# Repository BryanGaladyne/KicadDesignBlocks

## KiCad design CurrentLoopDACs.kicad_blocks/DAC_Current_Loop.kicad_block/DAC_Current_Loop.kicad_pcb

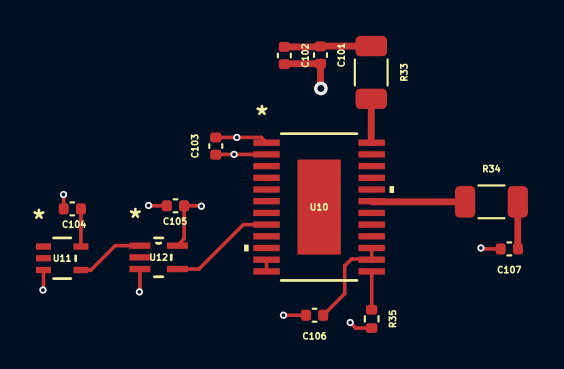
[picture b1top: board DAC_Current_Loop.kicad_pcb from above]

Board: 2 copper layers, 13 parts (0 on the bottom side), 11 nets.

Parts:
C101: 100p; C_0402_1005Metric
C102, C103, C104, C105, C106, C107: 0.1u; C_0402_1005Metric
R33: 10; R_1206_3216Metric
R34: 15; R_1206_3216Metric
R35: 15K; R_0402_1005Metric
U10: DAC7750IPWPR; PWP24_TEX
U11: NC7SZ04P5X; SC-88A-5_1P35X2P2_ONS
U12: SN74LVC1G08DCKR; DCK5

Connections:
+3.3VP: C103.1, C104.1, C105.1, U10.2 (DVDD), U11.5 (VCC), U12.5 (VCC)
+12V: C101.1, C102.1, R33.1
/DAC/AVDD: R33.2, U10.24 (AVDD)
/DAC/CURRENT_OUT: C107.1, R34.2
/DAC/IOUT: R34.1, U10.19 (IOUT)
/DAC/ISET_R: R35.1, U10.13 (ISET-R)
/DAC/LATCH: U10.7 (LATCH), U11.2 (A)
/DAC/LATCH_N: U11.4 (A_N=Y), U12.1 (A)
/DAC/REFOUT: C106.1, U10.14 (REFOUT), U10.15 (REFIN)
/DAC/SCLK_AND_LATCH_N: U10.8 (SCLK), U12.4 (Y)
GND: C101.2, C102.2, C103.2, C104.2, C105.2, C106.2, C107.2, R35.2, U10.1 (GND), U10.4 (GND), U10.5 (GND), U10.11 (GND), U10.12 (GND), U11.3 (GND), U12.3 (GND)

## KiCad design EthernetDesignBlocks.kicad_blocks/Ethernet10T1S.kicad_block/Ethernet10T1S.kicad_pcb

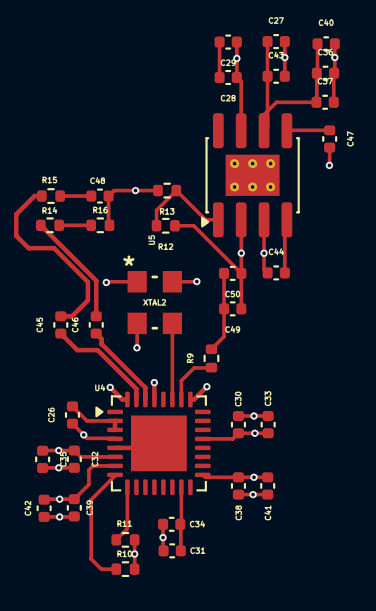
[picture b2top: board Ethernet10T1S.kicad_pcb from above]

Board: 2 copper layers, 36 parts (0 on the bottom side), 15 nets.

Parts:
C26, C27, C28, C29: 10u; C_0402_1005Metric
C30, C31, C32, C38, C39: 10n; C_0402_1005Metric
C33, C34, C35, C41, C42, C45, C46, C48: .1U; C_0402_1005Metric
C36, C37, C40, C43, C44, C47, C50: 1u; C_0402_1005Metric
C49: 100n; C_0402_1005Metric
R9: 12.4K; R_0402_1005Metric
R10, R11: 10K; R_0402_1005Metric
R12: 2.94K; R_0402_1005Metric
R13: 1.13K; R_0402_1005Metric
R14, R15: 49.9K; R_0402_1005Metric
R16: 100K; R_0402_1005Metric
U4: LAN8650B1-E/LMX; QFN-32-1EP_5x5mm_P0.5mm_EP3.1x3.1mm
U5: LP38852MRX-ADJ/NOPB; SOIC-8-1EP_3.9x4.9mm_P1.27mm_EP2.29x3mm_ThermalVias
XTAL2: ECS-2520S33-250-FN-TR; ECS-2520S_ECS

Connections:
+3V3: C26.1, C27.1, C28.1, C29.1, C36.1, C37.1, C38.1, C39.1, C40.1, C41.1, C42.1, C43.1, R10.2, R11.2, U4.4 (TEST), U4.7 (VDDP), U4.17 (VDDP), U4.25 (VDDAU), U4.29 (VDDA), U5.6 (EN), U5.7 (IN), XTAL2.1 (TRI-STATE), XTAL2.4 (VDD)
+5V: C44.1, U5.3 (BIAS)
/Ethernet2/1V8: C30.1, C31.1, C32.1, C33.1, C34.1, C35.1, C49.1, C50.1, R12.1, U4.6 (VDDC), U4.15 (VDDC), U4.21 (VDDC), U5.2 (OUT)
/Ethernet2/BIAS: R9.1, U4.26 (RBIAS)
/Ethernet2/ETH_10T1S_TRXN: C45.2, R15.1
/Ethernet2/ETH_10T1S_TRXP: C46.2, R14.1
/Ethernet2/IRQ_N: R11.1, U4.9 (IRQ_N)
/Ethernet2/RESET_N: R10.1, U4.8 (RESET_N)
/Ethernet2/TRXN: C45.1, U4.31 (TRXN)
/Ethernet2/TRXP: C46.1, U4.30 (TRXP)
/Ethernet2/U3_ADJ: R12.2, R13.1, U5.1 (ADJ)
/Ethernet2/U3_SS: C47.1, U5.5 (SS)
/Ethernet2/XTI_U2: U4.27 (XTI), XTAL2.3 (OUTPUT)
GND: C26.2, C27.2, C28.2, C29.2, C30.2, C31.2, C32.2, C33.2, C34.2, C35.2, C36.2, C37.2, C38.2, C39.2, C40.2, C41.2, C42.2, C43.2, C44.2, C47.2, C48.1, C49.2, C50.2, R9.2, R13.2, R16.2, U4.2 (VSS), U4.3 (VSS), U4.5 (VSS), U4.33 (VSS), U5.4 (GND), XTAL2.2 (GND)
unnamed: C48.2, R14.2, R15.2, R16.1

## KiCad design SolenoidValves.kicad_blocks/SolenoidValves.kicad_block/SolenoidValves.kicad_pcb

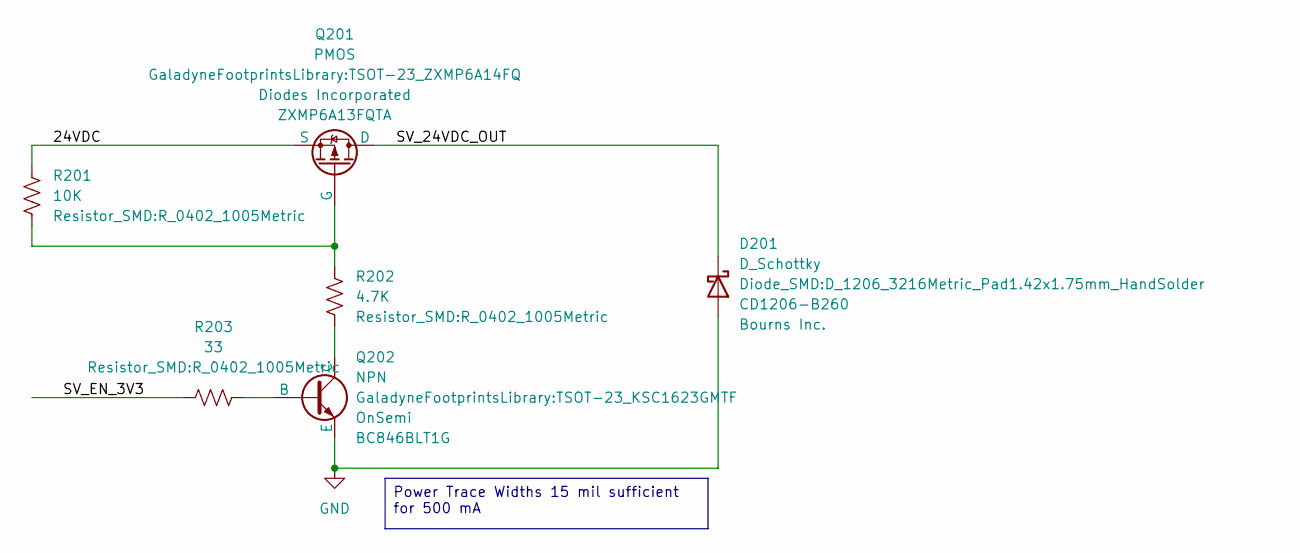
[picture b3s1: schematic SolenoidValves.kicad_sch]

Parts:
D201: D_Schottky; D_1206_3216Metric_Pad1.42x1.75mm_HandSolder; MPN CD1206-B260
Q201: PMOS; TSOT-23_ZXMP6A14FQ; MPN ZXMP6A13FQTA
Q202: NPN; TSOT-23_KSC1623GMTF; MPN BC846BLT1G
R201: 10K; R_0402_1005Metric
R202: 4.7K; R_0402_1005Metric
R203: 33; R_0402_1005Metric

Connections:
/SolenoidValves/24VDC: Q201.3 (S), R201.1
/SolenoidValves/SV_24VDC_OUT: D201.1 (K), Q201.1 (D)
/SolenoidValves/SV_EN_3V3: R203.1
GND: D201.2 (A), Q202.3 (E)
unnamed: Q201.2 (G), R201.2, R202.1
unnamed: Q202.2 (B), R203.2
unnamed: Q202.1 (C), R202.2

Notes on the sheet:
Power Trace Widths 15 mil sufficient for 500 mA

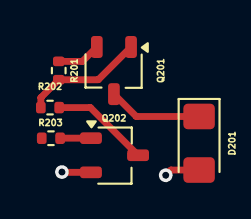
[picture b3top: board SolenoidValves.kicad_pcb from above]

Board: 2 copper layers, 6 parts (0 on the bottom side), 6 nets.

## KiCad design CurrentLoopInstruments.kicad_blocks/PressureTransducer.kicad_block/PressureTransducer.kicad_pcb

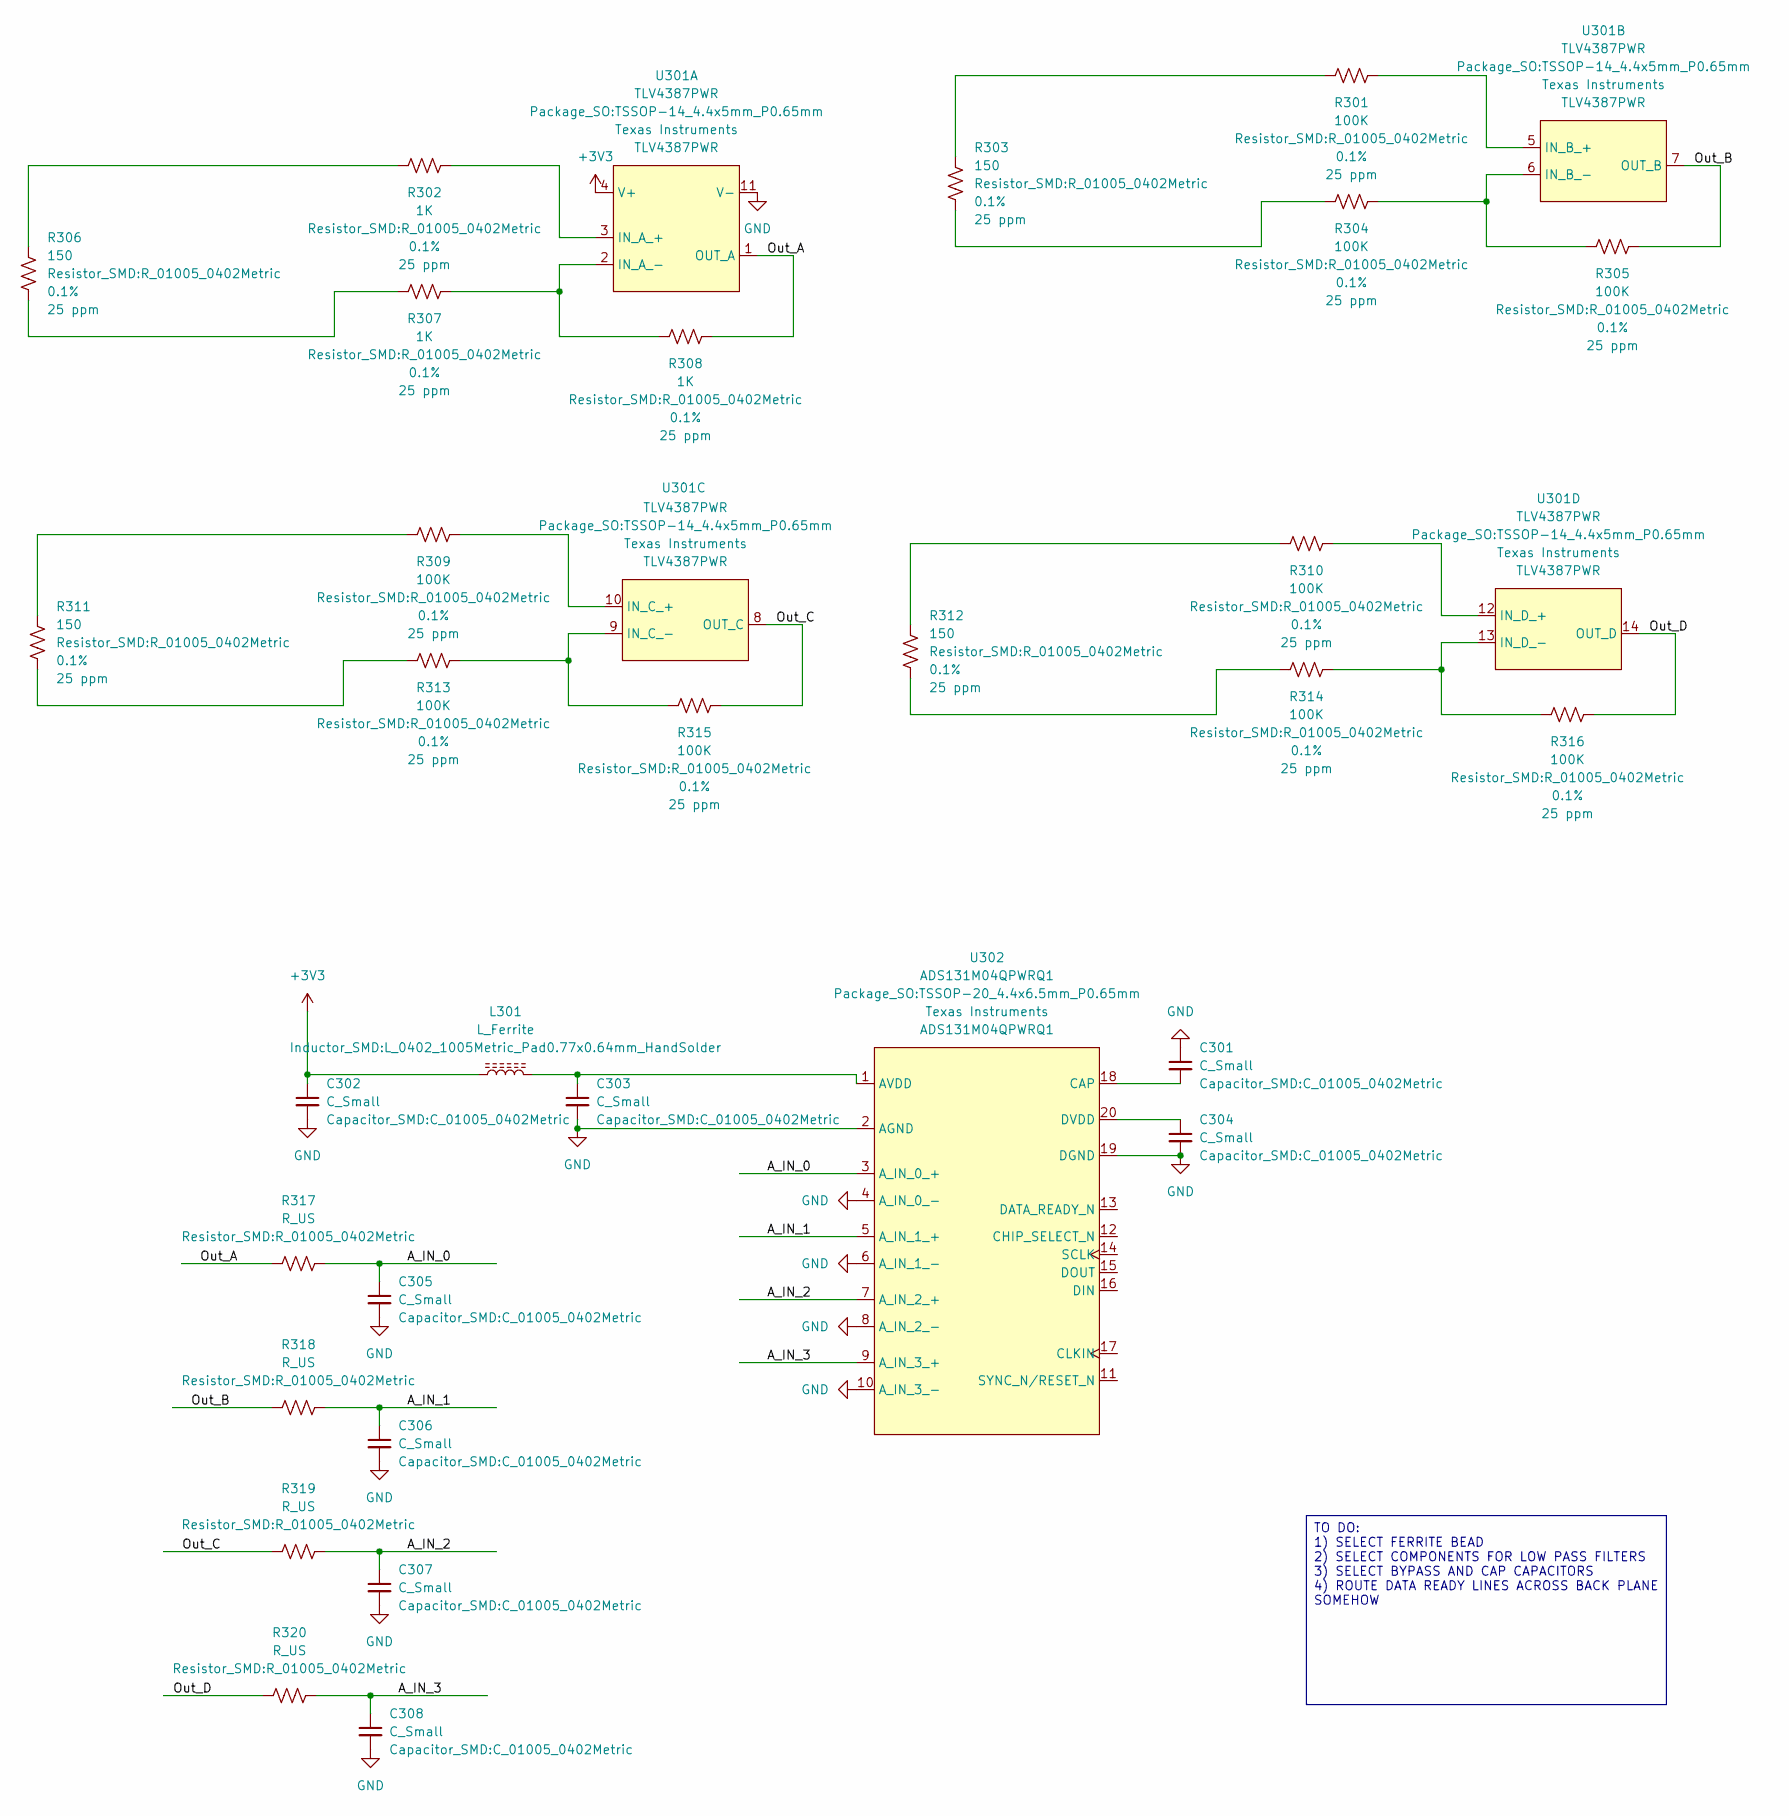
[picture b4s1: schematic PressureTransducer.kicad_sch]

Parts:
C301, C302, C303, C304, C305, C306, C307, C308: C_Small; C_01005_0402Metric
L301: L_Ferrite; L_0402_1005Metric_Pad0.77x0.64mm_HandSolder
R301, R304, R305, R309, R310, R313, R314, R315, R316: 100K; R_01005_0402Metric; Tolerance 0.1%
R302, R307, R308: 1K; R_01005_0402Metric; Tolerance 0.1%
R303, R306, R311, R312: 150; R_01005_0402Metric; Tolerance 0.1%
R317, R318, R319, R320: R_US; R_01005_0402Metric
U301: TLV4387PWR; TSSOP-14_4.4x5mm_P0.65mm; MPN TLV4387PWR
U302: ADS131M04QPWRQ1; TSSOP-20_4.4x6.5mm_P0.65mm; MPN ADS131M04QPWRQ1

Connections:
+3V3: C302.1, L301.1, U301.4 (V+)
/PressureTransducer/A_IN_0: C305.1, R317.2, U302.3 (A_IN_0_+)
/PressureTransducer/A_IN_1: C306.1, R318.2, U302.5 (A_IN_1_+)
/PressureTransducer/A_IN_2: C307.1, R319.2, U302.7 (A_IN_2_+)
/PressureTransducer/A_IN_3: C308.1, R320.2, U302.9 (A_IN_3_+)
/PressureTransducer/Out_A: R308.2, R317.1, U301.1 (OUT_A)
/PressureTransducer/Out_B: R305.2, R318.1, U301.7 (OUT_B)
/PressureTransducer/Out_C: R315.2, R319.1, U301.8 (OUT_C)
/PressureTransducer/Out_D: R316.2, R320.1, U301.14 (OUT_D)
GND: C301.1, C302.2, C303.2, C304.2, C305.2, C306.2, C307.2, C308.2, U301.11 (V-), U302.2 (AGND), U302.4 (A_IN_0_-), U302.6 (A_IN_1_-), U302.8 (A_IN_2_-), U302.10 (A_IN_3_-), U302.19 (DGND)
unnamed: R301.1, R303.2
unnamed: R302.1, R306.2
unnamed: R303.1, R304.1
unnamed: R306.1, R307.1
unnamed: R309.1, R311.2
unnamed: R310.1, R312.2
unnamed: R311.1, R313.1
unnamed: R312.1, R314.1
unnamed: R302.2, U301.3 (IN_A_+)
unnamed: R307.2, R308.1, U301.2 (IN_A_-)
unnamed: R301.2, U301.5 (IN_B_+)
unnamed: R304.2, R305.1, U301.6 (IN_B_-)
unnamed: R309.2, U301.10 (IN_C_+)
unnamed: R313.2, R315.1, U301.9 (IN_C_-)
unnamed: R310.2, U301.12 (IN_D_+)
unnamed: R314.2, R316.1, U301.13 (IN_D_-)
unnamed: C303.1, L301.2, U302.1 (AVDD)
unnamed: C301.2, U302.18 (CAP)
unnamed: C304.1, U302.20 (DVDD)

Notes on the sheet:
TO DO: 1) SELECT FERRITE BEAD 2) SELECT COMPONENTS FOR LOW PASS FILTERS 3) SELECT BYPASS AND CAP CAPACITORS 4) ROUTE DATA READY LINES ACROSS BACK PLANE SOMEHOW

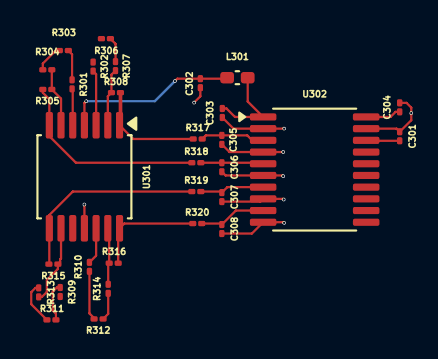
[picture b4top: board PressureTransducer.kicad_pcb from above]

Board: 2 copper layers, 31 parts (0 on the bottom side), 29 nets.

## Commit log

2026-04-16 commit current loop schematic and pcb layout design block v0p1
2026-04-16 add solenoid valves circuit
2026-04-16 ADD 10T1S PHY AND 1V8 SUPPLY BLOCK
2026-04-17 create current loop dac design blocks and pcb layout
